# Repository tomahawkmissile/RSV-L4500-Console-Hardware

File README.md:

# RSV-L4500-Console-Hardware
A console mounted on the front of the Rosewill RSV-L4500 server rackmount case

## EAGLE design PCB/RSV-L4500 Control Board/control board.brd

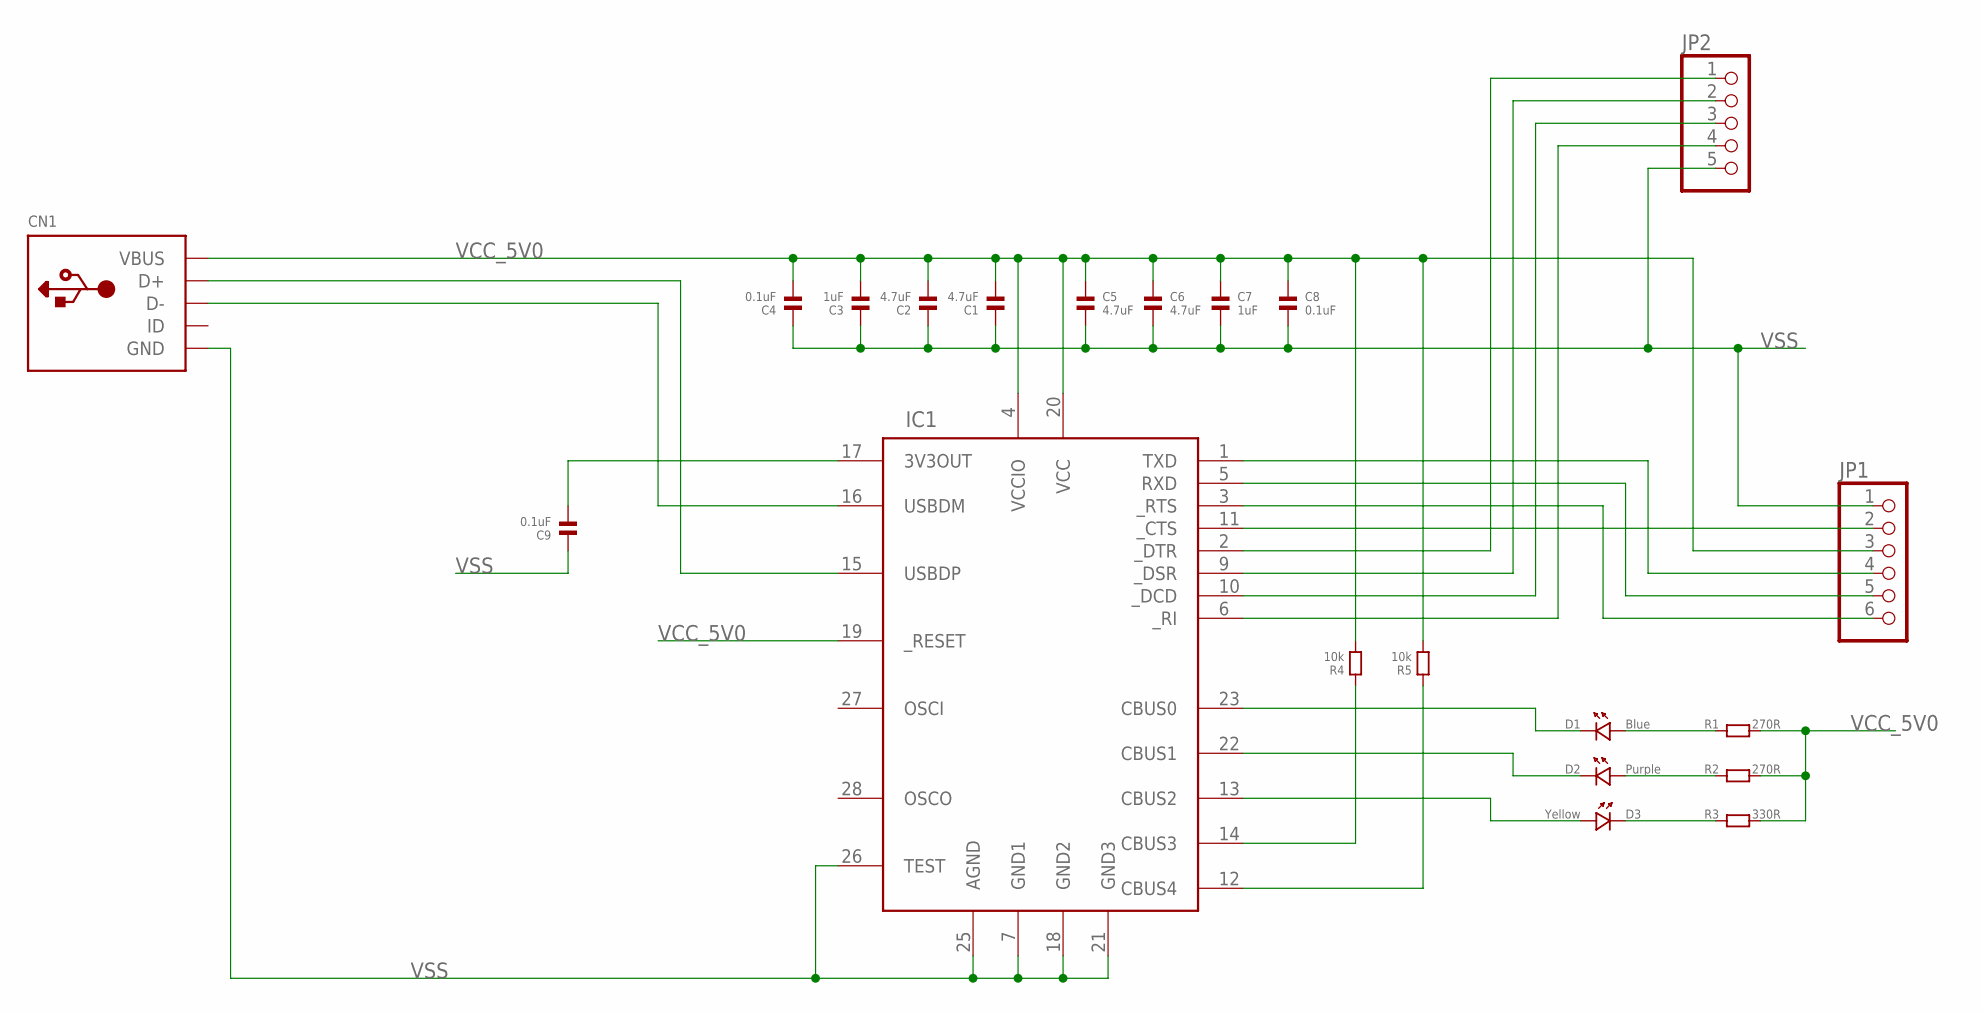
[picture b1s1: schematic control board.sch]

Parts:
C1, C2, C5, C6: 4.7uF; 0603
C3, C7: 1uF; 0603
C4, C8, C9: 0.1uF; 0603
CN1: USBMINIB; USB-MINIB
D1: Blue; 0603.LED
D2: Purple; 0603.LED
D3: Yellow; 0603.LED
IC1: FT232RL; SSOP28DB
JP1: PINHD-1X6; 1X06
JP2: PINHD-1X5; 1X05
R1, R2: 270R; 0603
R3: 330R; 0603
R4, R5: 10k; 0603

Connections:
unnamed: CN1.D-, IC1.16 (USBDM)
unnamed: CN1.D+, IC1.15 (USBDP)
unnamed: IC1.11 (_CTS), JP1.2
unnamed: IC1.1 (TXD), JP1.4
unnamed: IC1.5 (RXD), JP1.5
unnamed: IC1.3 (_RTS), JP1.6
unnamed: D1.P$2 (2), IC1.23 (CBUS0)
unnamed: D2.P$2 (2), IC1.22 (CBUS1)
unnamed: D2.P$1 (1), R2.1
unnamed: D1.P$1 (1), R1.1
unnamed: D3.P$1 (1), IC1.13 (CBUS2)
unnamed: IC1.14 (CBUS3), R4.1
unnamed: IC1.12 (CBUS4), R5.1
unnamed: D3.P$2 (2), R3.1
unnamed: IC1.6 (_RI), JP2.4
unnamed: C9.2, IC1.17 (3V3OUT)
unnamed: IC1.10 (_DCD), JP2.3
unnamed: IC1.9 (_DSR), JP2.2
unnamed: IC1.2 (_DTR), JP2.1
VCC_5V0: C1.2, C2.2, C3.2, C4.2, C5.1, C6.1, C7.1, C8.1, CN1.VBUS, IC1.4 (VCCIO), IC1.19 (_RESET), IC1.20 (VCC), JP1.3, R1.2, R2.2, R3.2, R4.2, R5.2
VSS: C1.1, C2.1, C3.1, C4.1, C5.2, C6.2, C7.2, C8.2, C9.1, CN1.GND, IC1.7 (GND1), IC1.18 (GND2), IC1.21 (GND3), IC1.25 (AGND), IC1.26 (TEST), JP1.1, JP2.5

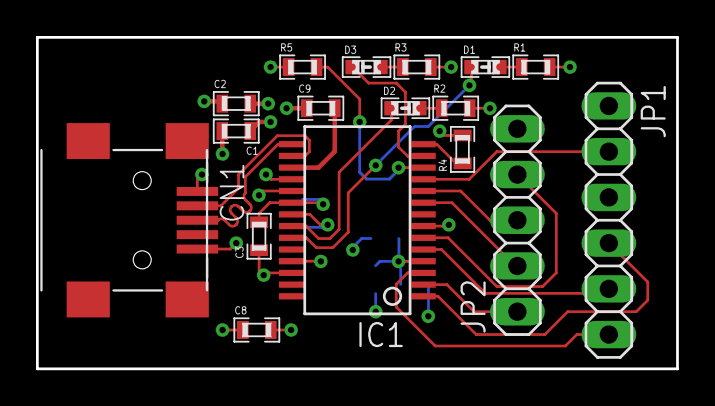
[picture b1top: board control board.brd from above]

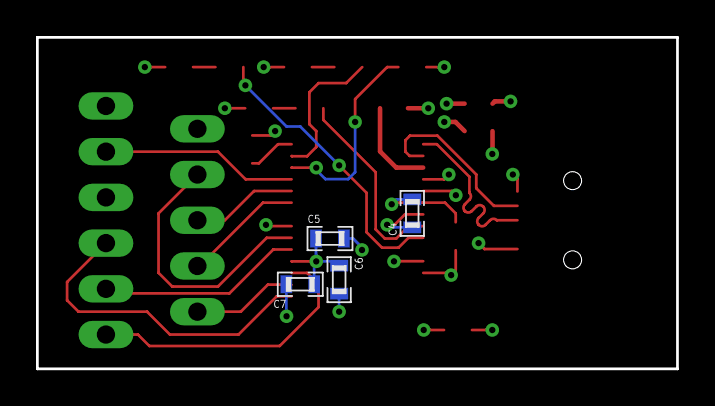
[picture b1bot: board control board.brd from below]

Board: 2 copper layers, 35.6 x 18.4 mm, 21 parts (4 on the bottom side), 21 nets.

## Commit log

2020-03-13 Added initial plate mount
2020-03-30 Upload initial design files
2020-10-05 Update README.md
    Fixed README formatting.
